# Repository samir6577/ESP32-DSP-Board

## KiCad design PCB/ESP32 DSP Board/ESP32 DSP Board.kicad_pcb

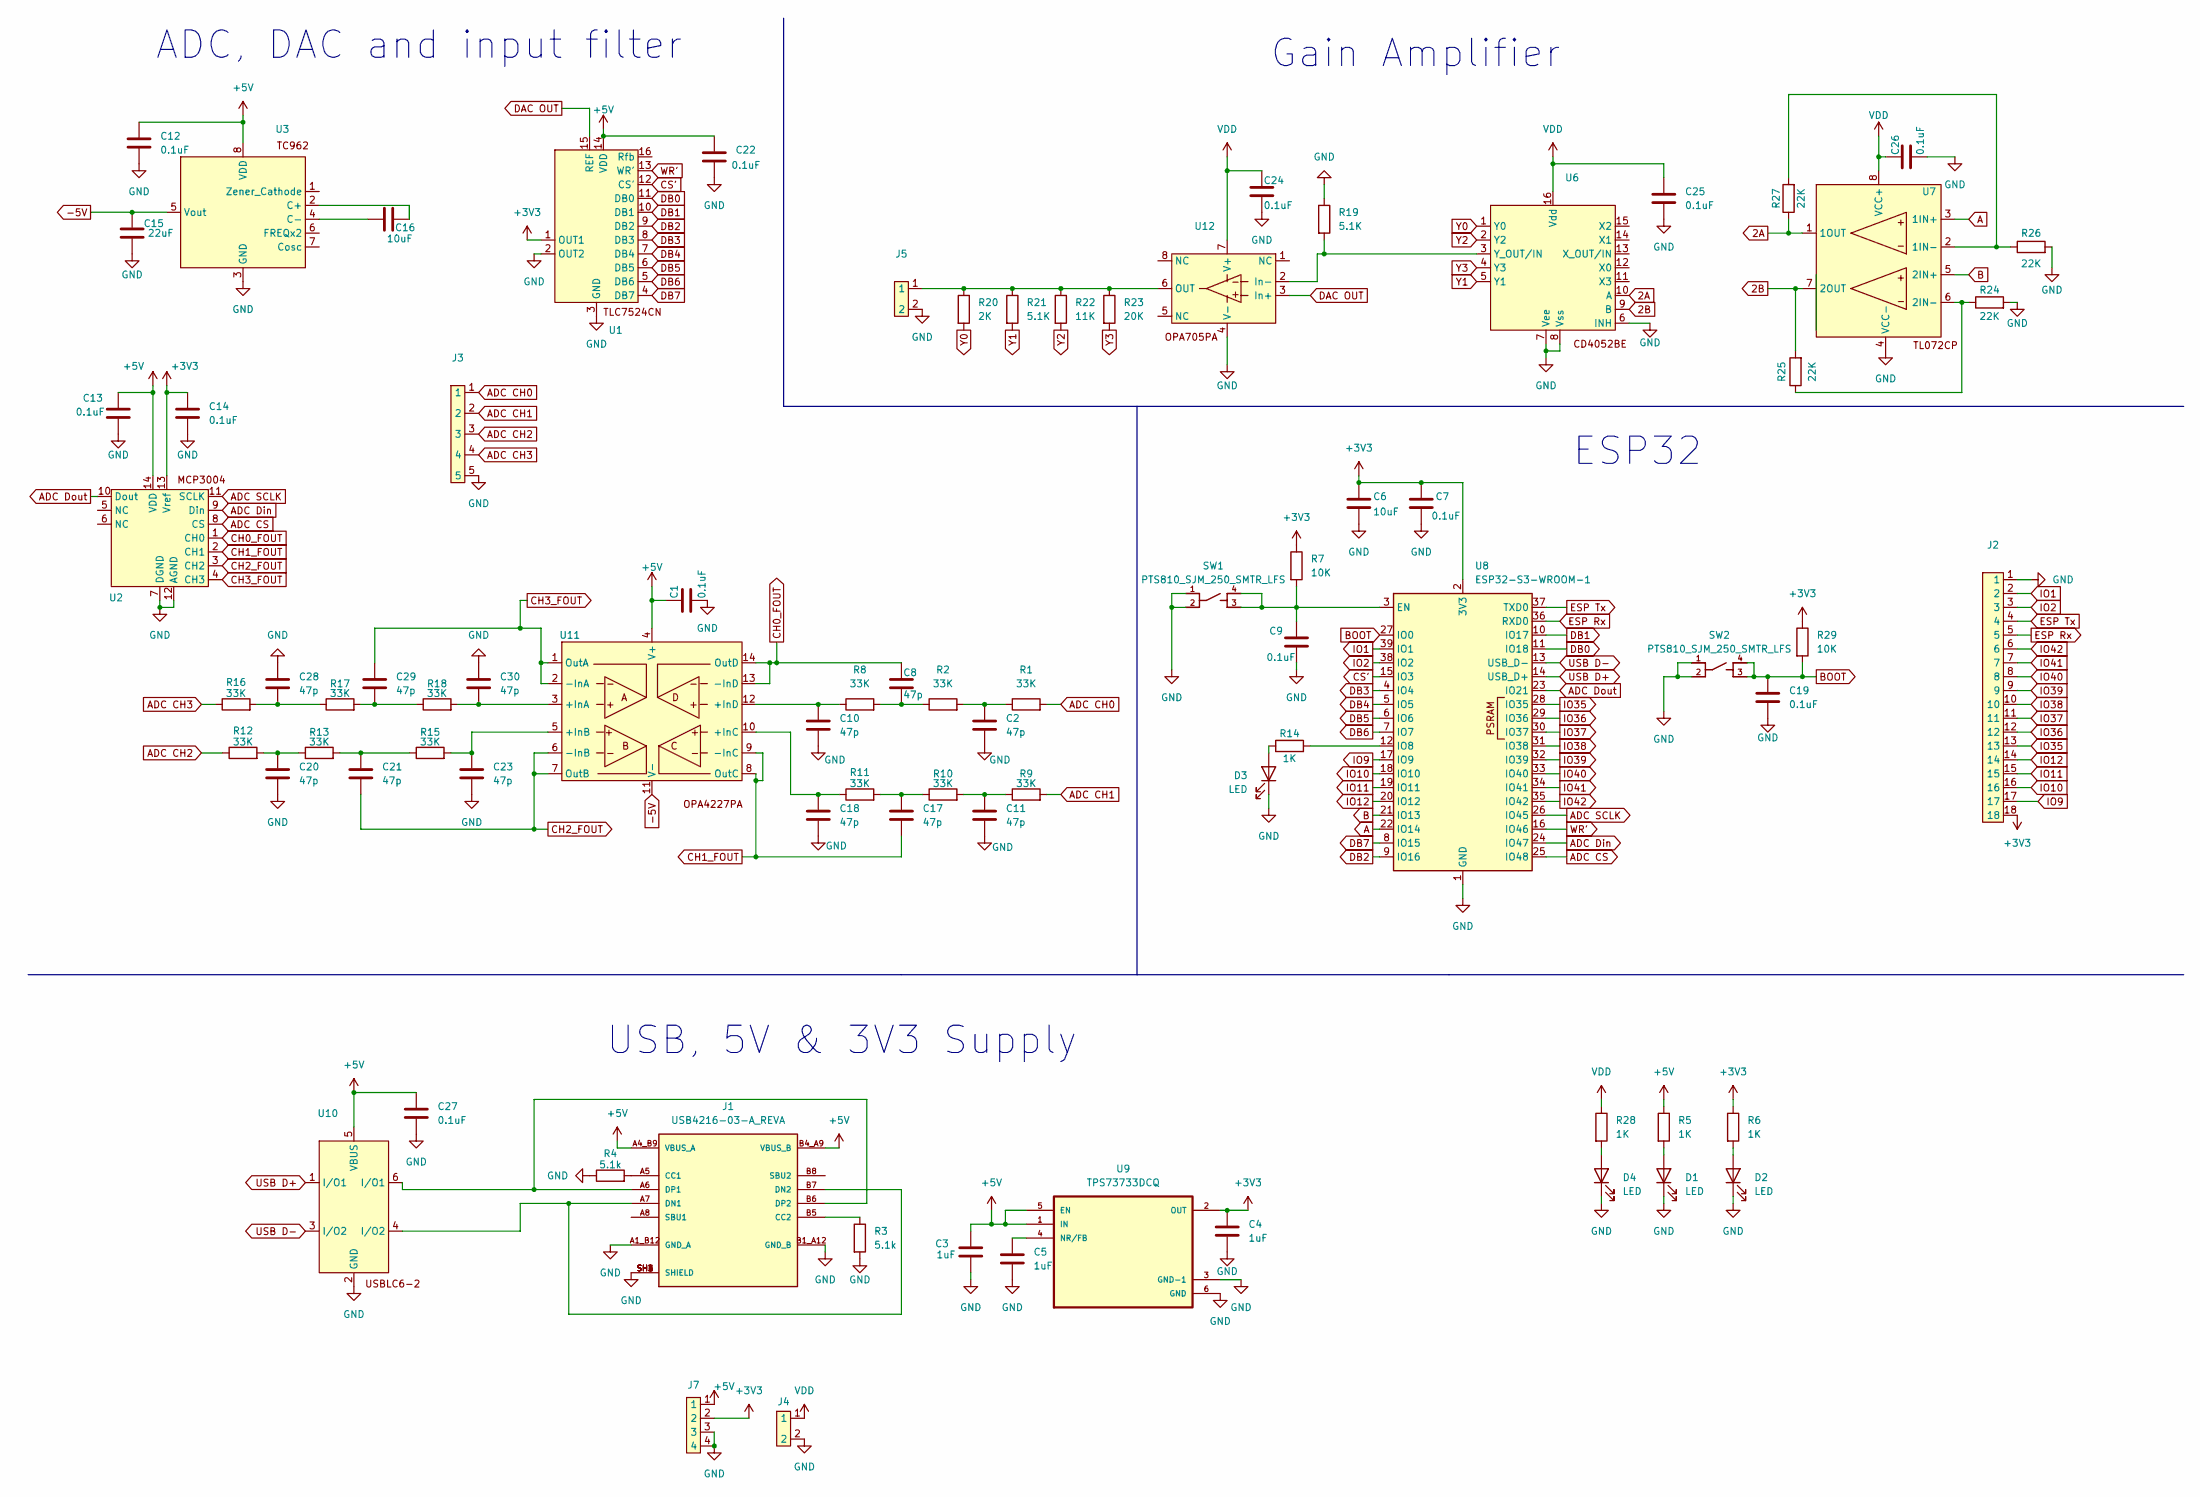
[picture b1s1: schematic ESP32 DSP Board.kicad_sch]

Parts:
C1, C7, C9, C12, C13, C14, C19, C22, C24, C25, C26, C27: 0.1uF; C_1206_3216Metric_Pad1.33x1.80mm_HandSolder
C2, C8, C10, C11, C17, C18, C20, C21, C23, C28, C29, C30: 47p; C_1206_3216Metric_Pad1.33x1.80mm_HandSolder
C3, C4, C5: 1uF; C_1206_3216Metric_Pad1.33x1.80mm_HandSolder
C6, C16: 10uF; C_1206_3216Metric_Pad1.33x1.80mm_HandSolder
C15: 22uF; CP_Radial_Tantal_D4.5mm_P2.50mm
D1, D2, D3, D4: LED; LED_1206_3216Metric_Pad1.42x1.75mm_HandSolder
J1: USB4216-03-A_REVA; GCT_USB4216-03-A_REVA; PARTREV A
J2: PinHeader_1x18_P2.54mm_Vertical
J3: PinHeader_1x05_P2.54mm_Vertical
J4, J5: PinHeader_1x02_P2.54mm_Vertical
J7: PinHeader_1x04_P2.54mm_Vertical
R1, R2, R8, R9, R10, R11, R12, R13, R15, R16, R17, R18: 33K; R_1206_3216Metric_Pad1.30x1.75mm_HandSolder
R3, R4: 5.1k; R_1206_3216Metric_Pad1.30x1.75mm_HandSolder
R5, R6, R14, R28: 1K; R_1206_3216Metric_Pad1.30x1.75mm_HandSolder
R7, R29: 10K; R_1206_3216Metric_Pad1.30x1.75mm_HandSolder
R19, R21: 5.1K; R_1206_3216Metric_Pad1.30x1.75mm_HandSolder
R20: 2K; R_1206_3216Metric_Pad1.30x1.75mm_HandSolder
R22: 11K; R_1206_3216Metric_Pad1.30x1.75mm_HandSolder
R23: 20K; R_1206_3216Metric_Pad1.30x1.75mm_HandSolder
R24, R25, R26, R27: 22K; R_1206_3216Metric_Pad1.30x1.75mm_HandSolder
SW1, SW2: PTS810_SJM_250_SMTR_LFS; SW_PTS810_SJM_250_SMTR_LFS
U1, U6: DIP-16_W7.62mm
U2: DIP-14_W7.62mm
U3, U7, U12: DIP-8_W7.62mm
U8: ESP32-S3-WROOM-1
U9: TPS73733DCQ
U10: USBLC6-2P6
U11: CERDIP-14_W7.62mm_SideBrazed

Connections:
2A: R27.1, U6.10 (A), U7.1 (1OUT)
2B: R25.2, U6.9 (B), U7.7 (2OUT)
+3V3: C4.1, C6.1, C7.1, C14.1, J2.18, J7.2, R6.1, R7.1, R29.1, U1.1 (OUT1), U2.13 (Vref), U8.2 (3V3), U9.2 (OUT)
+5V: C1.1, C3.1, C12.1, C13.1, C22.1, C27.1, J1.A4_B9 (VBUS_A), J1.B4_A9 (VBUS_B), J7.1, R5.1, U1.14 (VDD), U2.14 (VDD), U3.8 (VDD), U9.1 (IN), U9.5 (EN), U10.5 (VBUS), U11.4 (V+)
-5V: C15.1, U3.5 (Vout), U11.11 (V-)
A: U7.3 (1IN+), U8.22 (IO14)
ADC CH0: J3.1, R1.2
ADC CH1: J3.2, R9.2
ADC CH2: J3.3, R12.1
ADC CH3: J3.4, R16.1
ADC CS: U2.8 (CS), U8.25 (IO48)
ADC Din: U2.9 (Din), U8.24 (IO47)
ADC Dout: U2.10 (Dout), U8.23 (IO21)
ADC SCLK: U2.11 (SCLK), U8.26 (IO45)
B: U7.5 (2IN+), U8.21 (IO13)
BOOT: C19.1, R29.2, SW2.3, SW2.4, U8.27 (IO0)
CH0_FOUT: C8.1, U2.1 (CH0), U11.13 (-InD), U11.14 (OutD)
CH1_FOUT: C17.2, U2.2 (CH1), U11.8 (OutC), U11.9 (-InC)
CH2_FOUT: C21.2, U2.3 (CH2), U11.6 (-InB), U11.7 (OutB)
CH3_FOUT: C29.1, U2.4 (CH3), U11.1 (OutA), U11.2 (-InA)
CS': U1.12 (CS'), U8.15 (IO3)
DAC OUT: U1.15 (REF), U12.3 (In+)
DB0: U1.11 (DB0), U8.11 (IO18)
DB1: U1.10 (DB1), U8.10 (IO17)
DB2: U1.9 (DB2), U8.9 (IO16)
DB3: U1.8 (DB3), U8.4 (IO4)
DB4: U1.7 (DB4), U8.5 (IO5)
DB5: U1.6 (DB5), U8.6 (IO6)
DB6: U1.5 (DB6), U8.7 (IO7)
DB7: U1.4 (DB7), U8.8 (IO15)
ESP Rx: J2.5, U8.36 (RXD0)
ESP Tx: J2.4, U8.37 (TXD0)
GND: C1.2, C2.2, C3.2, C4.2, C5.2, C6.2, C7.2, C9.2, C10.2, C11.2, C12.2, C13.2, C14.2, C15.2, C18.2, C19.2, C20.2, C22.2, C23.2, C24.2, C25.2, C26.2, C27.2, C28.1, C30.1, D1.1 (K), D2.1 (K), D3.1 (K), D4.1 (K), J1.A1_B12 (GND_A), J1.B1_A12 (GND_B), J1.SH1 (SHIELD), J1.SH2 (SHIELD), J1.SH3 (SHIELD), J1.SH4 (SHIELD), J2.1, J3.5, J4.2, J5.2, J7.3, J7.4, R3.2, R4.1, R19.1, R24.2, R26.2, SW1.1, SW1.2, SW2.1, SW2.2, U1.2 (OUT2), U1.3 (GND), U2.7 (DGND), U2.12 (AGND), U3.3 (GND), U6.6 (INH), U6.7 (Vee), U6.8 (Vss), U7.4 (VCC-), U8.1 (GND), U8.40 (GND), U8.41 (GND), U9.3 (GND-1), U9.6 (GND), U10.2 (GND), U12.4 (V-)
IO1: J2.2, U8.39 (IO1)
IO2: J2.3, U8.38 (IO2)
IO9: J2.17, U8.17 (IO9)
IO10: J2.16, U8.18 (IO10)
IO11: J2.15, U8.19 (IO11)
IO12: J2.14, U8.20 (IO12)
IO35: J2.13, U8.28 (IO35)
IO36: J2.12, U8.29 (IO36)
IO37: J2.11, U8.30 (IO37)
IO38: J2.10, U8.31 (IO38)
IO39: J2.9, U8.32 (IO39)
IO40: J2.8, U8.33 (IO40)
IO41: J2.7, U8.34 (IO41)
IO42: J2.6, U8.35 (IO42)
unnamed: C2.1, R1.1, R2.2
unnamed: C8.2, R2.1, R8.2
unnamed: C11.1, R9.1, R10.2
unnamed: C17.1, R10.1, R11.2
unnamed: C20.1, R12.2, R13.1
unnamed: C21.1, R13.2, R15.1
unnamed: C28.2, R16.2, R17.1
unnamed: C29.2, R17.2, R18.1
unnamed: D1.2 (A), R5.2
unnamed: D2.2 (A), R6.2
unnamed: D3.2 (A), R14.1
unnamed: D4.2 (A), R28.2
unnamed: J1.A5 (CC1), R4.2
unnamed: J1.B5 (CC2), R3.1
unnamed: J1.A7 (DN1), J1.B7 (DN2), U10.4 (I/O2)
unnamed: J1.A6 (DP1), J1.B6 (DP2), U10.6 (I/O1)
unnamed: C16.2, U3.2 (C+)
unnamed: C16.1, U3.4 (C-)
unnamed: R26.1, R27.2, U7.2 (1IN-)
unnamed: R24.1, R25.1, U7.6 (2IN-)
unnamed: C9.1, R7.2, SW1.3, SW1.4, U8.3 (EN)
unnamed: R14.2, U8.12 (IO8)
unnamed: C5.1, U9.4 (NR/FB)
unnamed: C30.2, R18.2, U11.3 (+InA)
unnamed: C23.1, R15.2, U11.5 (+InB)
unnamed: C18.1, R11.1, U11.10 (+InC)
unnamed: C10.1, R8.1, U11.12 (+InD)
unnamed: R19.2, U6.3 (Y_OUT/IN), U12.2 (In-)
unnamed: J5.1, R20.1, R21.1, R22.1, R23.1, U12.6 (OUT)
USB D+: U8.14 (USB_D+), U10.1 (I/O1)
USB D-: U8.13 (USB_D-), U10.3 (I/O2)
VDD: C24.1, C25.1, C26.1, J4.1, R28.1, U6.16 (Vdd), U7.8 (VCC+), U12.7 (V+)
WR': U1.13 (WR'), U8.16 (IO46)
Y0: R20.2, U6.1 (Y0)
Y1: R21.2, U6.5 (Y1)
Y2: R22.2, U6.2 (Y2)
Y3: R23.2, U6.4 (Y3)

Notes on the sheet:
ESP32
USB, 5V & 3V3 Supply
ADC, DAC and input filter
Gain Amplifier

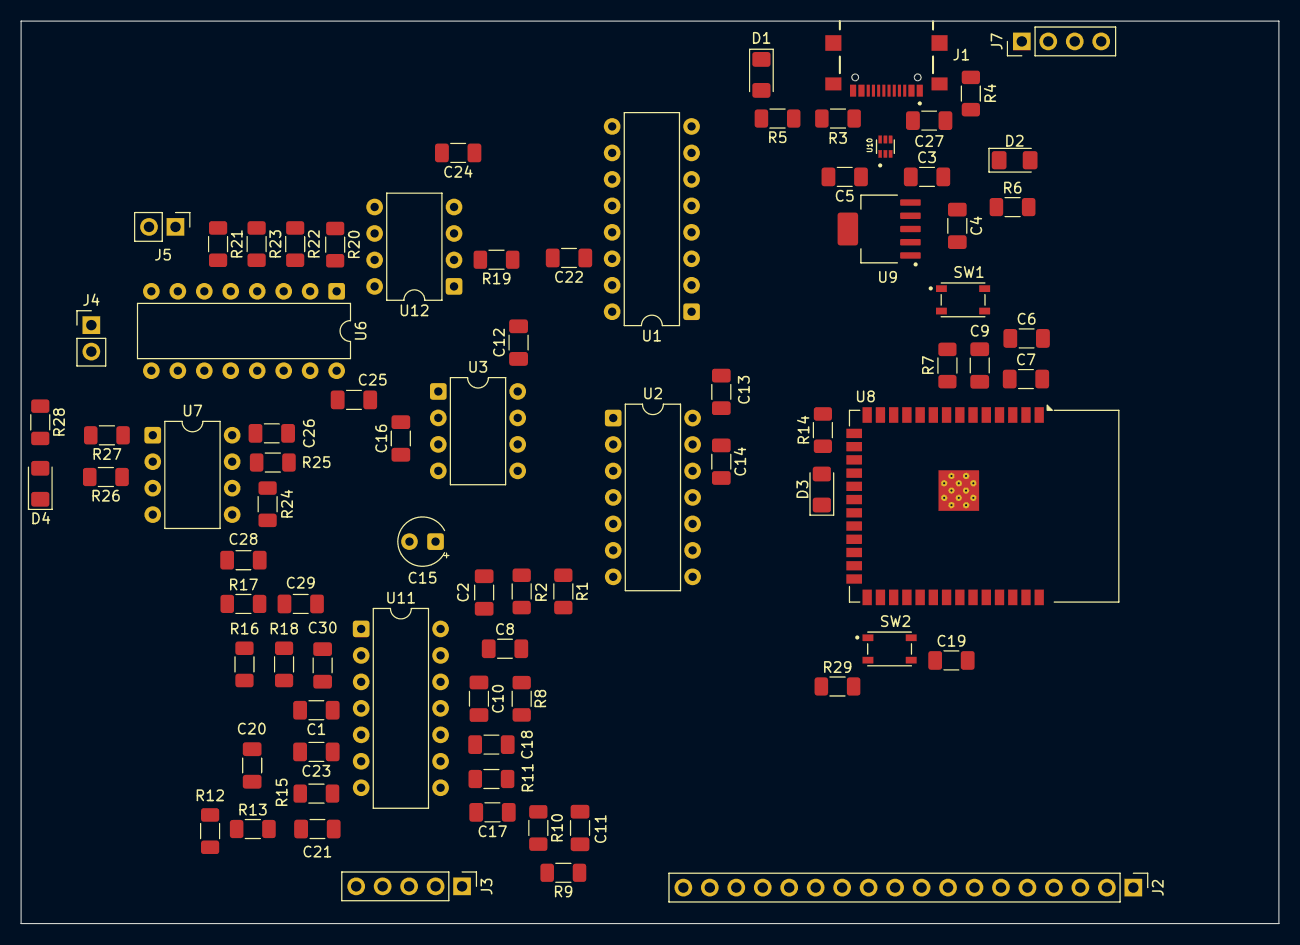
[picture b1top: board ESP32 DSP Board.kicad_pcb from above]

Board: 6 copper layers, 120.7 x 86.6 mm, 81 parts (0 on the bottom side), 84 nets.

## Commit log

2025-10-05 Added KiCad PCB and folder for simulations
2025-10-10 Schematic updates
2025-10-12 Schematic updates, added USB-UART bridge and tC962
2025-10-13 Schematic updates, ADC, DAC, and amplifiers
2025-10-15 Schematic first rev complete
2025-10-28 Schematic finished, footprints associated to components, PCB updated from schematic
2025-11-01 Added clamping and biasing to audio inputs, hpf and rail to rail amplifier to DAC output, 1.5V LDO, footprints updated
2025-11-02 PCB started, layers etup, analog layout started
2025-11-03 pcb component layout finished, ic and pin header footprints fixed
2025-11-08 U3 and U4 routing completed, 5V and GND plane added
2025-11-09 Analog Side Routing Complete
2025-11-15 Layer stackup changed to 6 layers, DAC routing started
2025-11-16 Digital layout changed, pins moved closer to mcu, routing completed before checks
2025-11-19 PCB finished pre-review
2025-11-20 Silkscreen added to connectors
2025-11-21 Power plane split into 5V and 3V3, USB connector moved to board edge, added stitching vias
2025-11-23 Mounting holes added, bom and manufacturing files generated
2025-11-24 all vias changed to through hole vias, production files re exported
2026-04-12 Input filter altered, output amplifier fixed, 22uf decoupling added to charge pump negative output
2026-04-14 Footprints changed to 1206 for resistors and capacitors, PCB restarted
2026-05-03 latest commit before laptop migration
